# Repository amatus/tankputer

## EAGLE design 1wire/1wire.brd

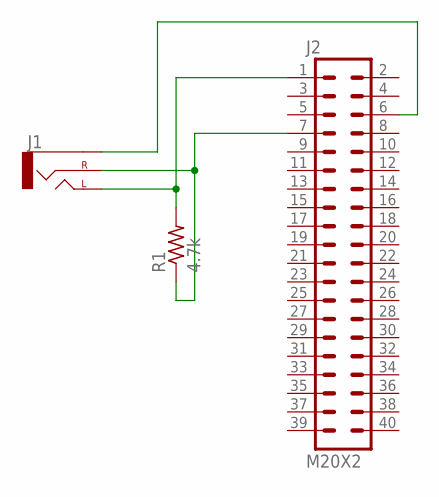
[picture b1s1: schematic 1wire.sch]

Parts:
J1: AUDIO-JACKPTH; AUDIO-JACK
J2: M20X2; 2X20
R1: 4.7k; R1206

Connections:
unnamed: J1.TIP (LEFT), J2.1, R1.2
unnamed: J1.RING (RIGHT), J2.7, R1.1
unnamed: J1.SLEEVE, J2.6

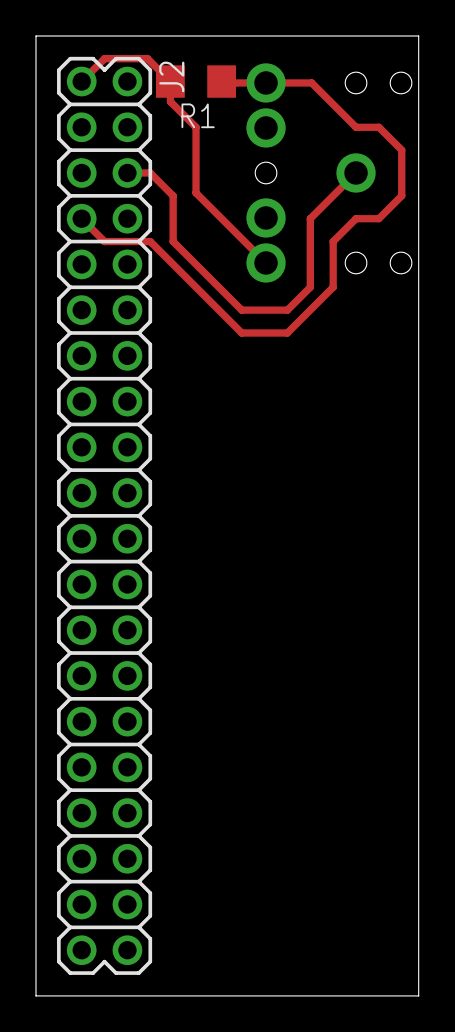
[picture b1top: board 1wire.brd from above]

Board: 2 copper layers, 21.3 x 53.3 mm, 3 parts (1 on the bottom side), 3 nets.

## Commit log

2016-09-10 Add 1wire board
2016-11-25 Starting point for hoplon app
2016-12-03 Add Semantic-UI and get blockly working
2016-12-04 Switch to cljsjs/semantic-ui
2016-12-04 Playing with castra
2016-12-04 Blockly libs are not foreign
2016-12-04 But I still can't get it working with optimization
2017-01-03 Optimization works!
2017-01-08 Start on a Cyclades Portmaster driver
2017-01-14 Read status and turn on/off ports
2017-01-14 Handle boot prompt
2017-01-16 Read temperature from Dallas DS18B20 sensors
2017-04-22 Fix unresolved symbol
2017-04-22 Call init for temperature and portmaster
2017-04-22 Fix typo
2017-04-22 Add state-fn
2017-04-23 I hate termios
2017-04-23 STFU
2017-04-23 Portmaster control and temp display

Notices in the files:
parts and their libraries:
SparkFun-Connectors: Licensing: Creative Commons ShareAlike 4.0 International - https://creativecommons.org/licenses/by-sa/4.0
